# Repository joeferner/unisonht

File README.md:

# Development

## Raspberry Pi

1.  Write the latest "Raspberry Pi OS Lite" to an SD Card (enable SSH, SSH key authentication, and note the hostname)
1.  Start the Raspberry Pi, open a command prompt and `ping <hostname>.local`
1.  Open a terminal

        ssh <username>@<host>.local
        sudo apt -y install git
        # copy id_rsa from host computer
        chmod 600 ~/.ssh/id_rsa
        ssh-keygen -p -f ~/.ssh/id_rsa # remove password
        git clone git@github.com:joeferner/unisonht.git
        ./unisonht/scripts/raspberry-pi-setup.sh

1.  Install "Remote Development" extension pack for VSCode.
1.  Connect VSCode via ssh (Ctrl+Shift+P -> Remote-SSH: Connect to Host...) `<username>@<host>.local`

# Development

```
./scripts/start-dev.sh
```

# IR Remote Control

```
ir-keytable # find gpio_ir_recv and note the rcX and use it in the next command
ir-keytable -s rc1 -t -c -p all
```

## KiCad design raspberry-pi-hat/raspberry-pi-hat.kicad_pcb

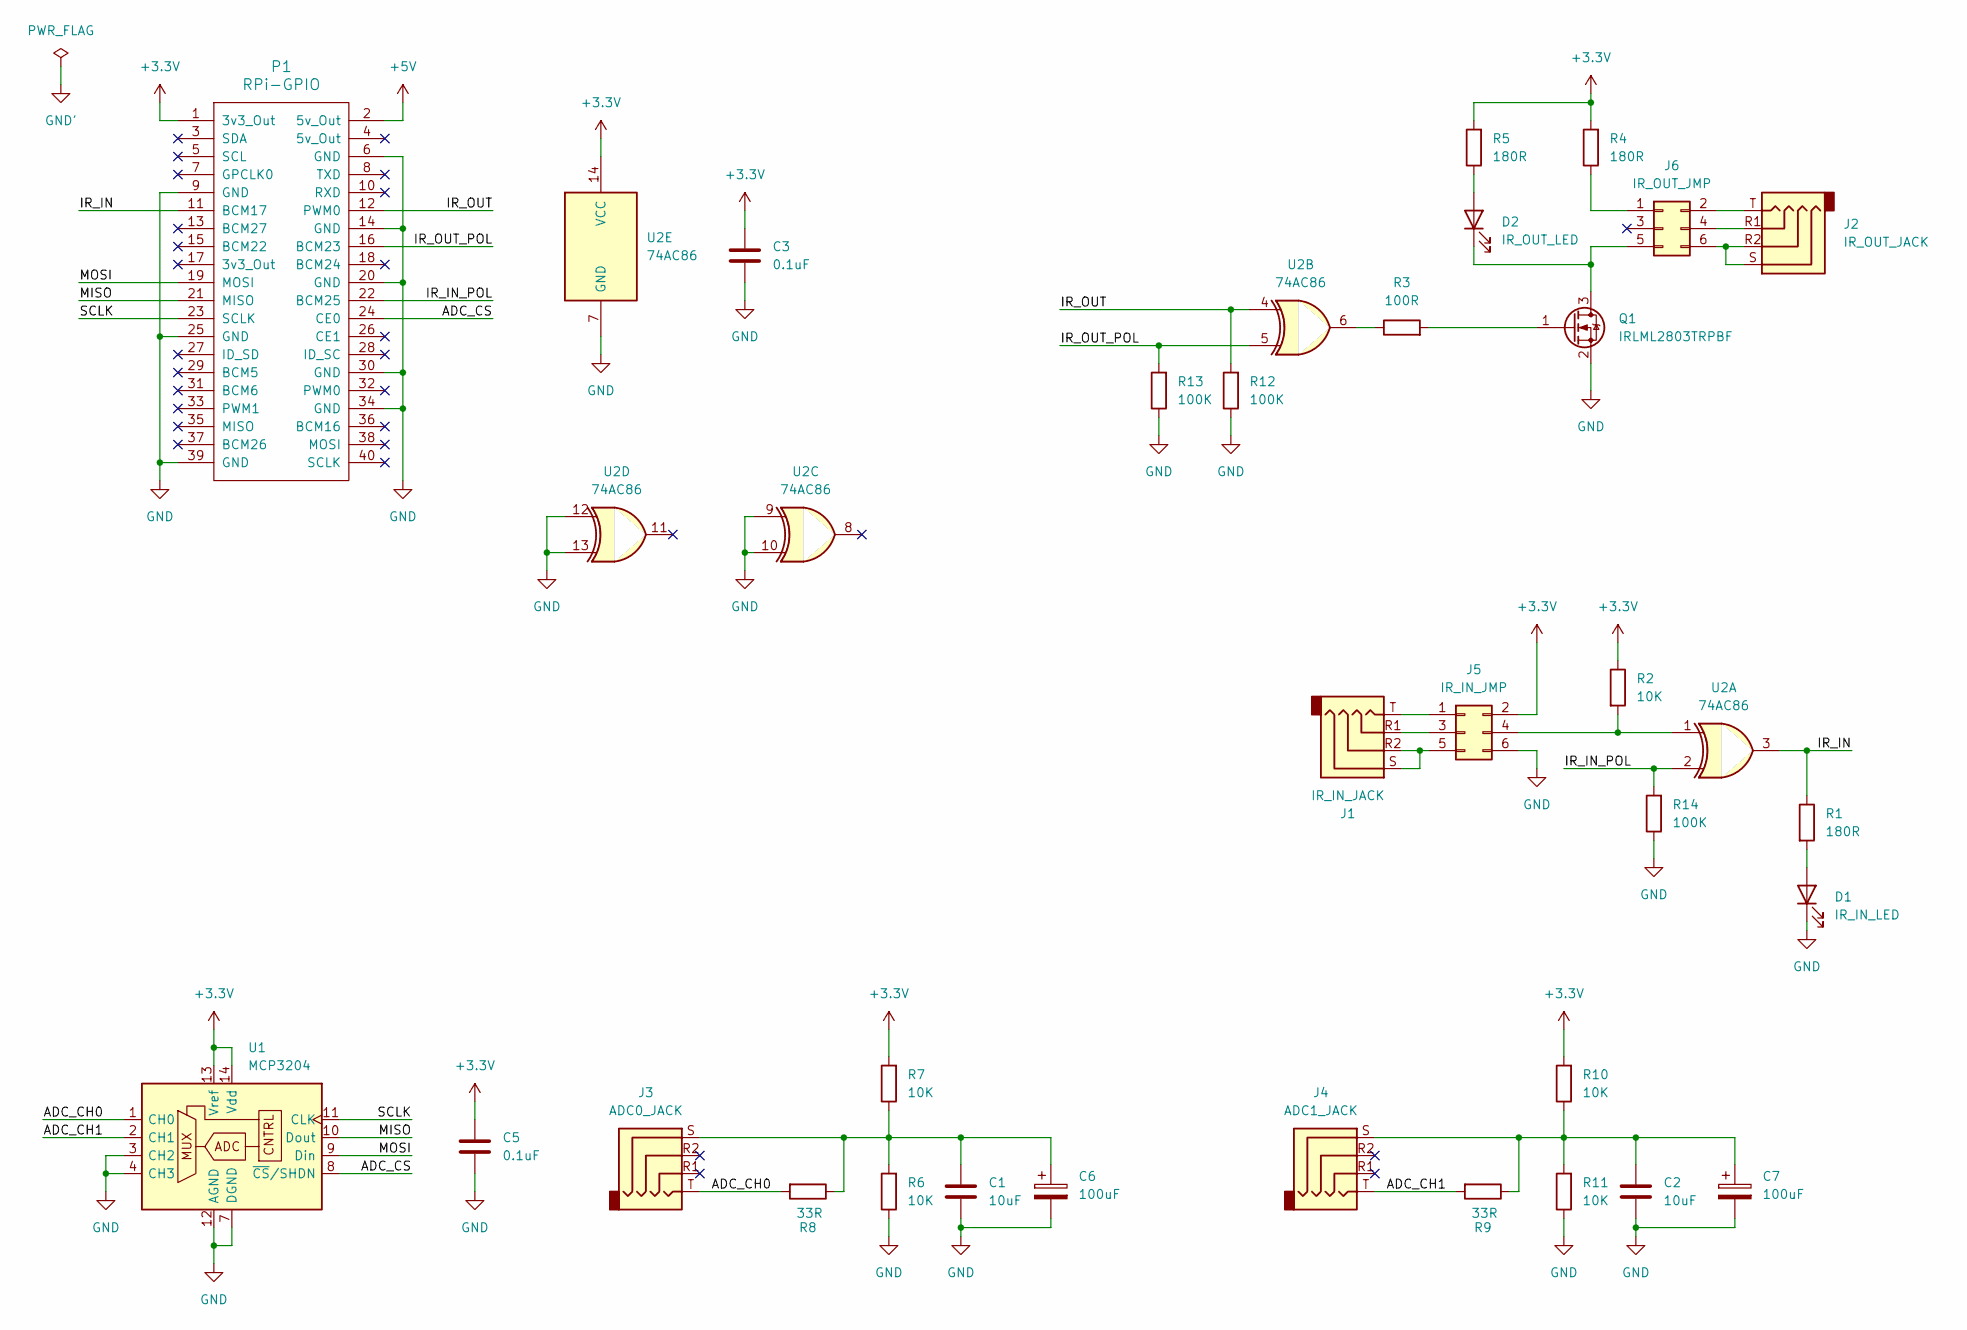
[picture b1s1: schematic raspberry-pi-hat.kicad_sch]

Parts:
C1, C2: 10uF; C_0805_2012Metric_Pad1.18x1.45mm_HandSolder
C3, C5: 0.1uF; C_0805_2012Metric_Pad1.18x1.45mm_HandSolder
C6, C7: 100uF; CP_Elec_5x5.3
D1: IR_IN_LED; LED_0805_2012Metric_Pad1.15x1.40mm_HandSolder
D2: IR_OUT_LED; LED_0805_2012Metric_Pad1.15x1.40mm_HandSolder
J1: IR_IN_JACK; 54-00174_TEN
J2: IR_OUT_JACK; 54-00174_TEN
J3: ADC0_JACK; 54-00174_TEN
J4: ADC1_JACK; 54-00174_TEN
J5: IR_IN_JMP; PinHeader_2x03_P2.54mm_Vertical
J6: IR_OUT_JMP; PinHeader_2x03_P2.54mm_Vertical
P1: RPi-GPIO; PinHeader_2x20_P2.54mm_Vertical
Q1: IRLML2803TRPBF; SOT-23
R1, R4, R5: 180R; R_0805_2012Metric_Pad1.20x1.40mm_HandSolder
R2, R6, R7, R10, R11: 10K; R_0805_2012Metric_Pad1.20x1.40mm_HandSolder
R3: 100R; R_0805_2012Metric_Pad1.20x1.40mm_HandSolder
R8, R9: 33R; R_0805_2012Metric_Pad1.20x1.40mm_HandSolder
R12, R13, R14: 100K; R_0805_2012Metric_Pad1.20x1.40mm_HandSolder
U1: MCP3204; SOIC-14_3.9x8.7mm_P1.27mm
U2: 74AC86; SOIC-14_3.9x8.7mm_P1.27mm

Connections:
+3.3V: C3.1, C5.1, J5.2, P1.1 (3v3_Out), R2.1, R4.2, R5.2, R7.2, R10.2, U1.13 (Vref), U1.14 (Vdd), U2.14 (VCC)
+5V: P1.2 (5v_Out)
/ADC_CH0: J3.T, R8.2, U1.1 (CH0)
/ADC_CH1: J4.T, R9.2, U1.2 (CH1)
/ADC_CS: P1.24 (CE0), U1.8 (~CS/SHDN)
/IR_IN: P1.11 (BCM17), R1.1, U2.3
/IR_IN_POL: P1.22 (BCM25), R14.2, U2.2
/IR_OUT: P1.12 (PWM0), R12.2, U2.4
/IR_OUT_POL: P1.16 (BCM23), R13.2, U2.5
/MISO: P1.21 (MISO), U1.10 (Dout)
/MOSI: P1.19 (MOSI), U1.9 (Din)
/SCLK: P1.23 (SCLK), U1.11 (CLK)
GND: C1.2, C2.2, C3.2, C5.2, C6.2, C7.2, D1.1 (K), J5.6, P1.6 (GND), P1.9 (GND), P1.14 (GND), P1.20 (GND), P1.25 (GND), P1.30 (GND), P1.34 (GND), P1.39 (GND), Q1.2 (S), R6.1, R11.1, R12.1, R13.1, R14.1, U1.3 (CH2), U1.4 (CH3), U1.7 (DGND), U1.12 (AGND), U2.7 (GND), U2.9, U2.10, U2.12, U2.13
unnamed: C1.1, C6.1, J3.S, R6.2, R7.1, R8.1
unnamed: C2.1, C7.1, J4.S, R9.1, R10.1, R11.2
unnamed: D1.2 (A), R1.2
unnamed: D2.2 (A), R5.1
unnamed: D2.1 (K), J6.5, Q1.3 (D)
unnamed: J1.T, J5.1
unnamed: J1.R1, J5.3
unnamed: J5.4, R2.2, U2.1
unnamed: J1.R2, J1.S, J5.5
unnamed: J6.1, R4.1
unnamed: J2.T, J6.2
unnamed: J2.R1, J6.4
unnamed: J2.R2, J2.S, J6.6
unnamed: Q1.1 (G), R3.2
unnamed: R3.1, U2.6

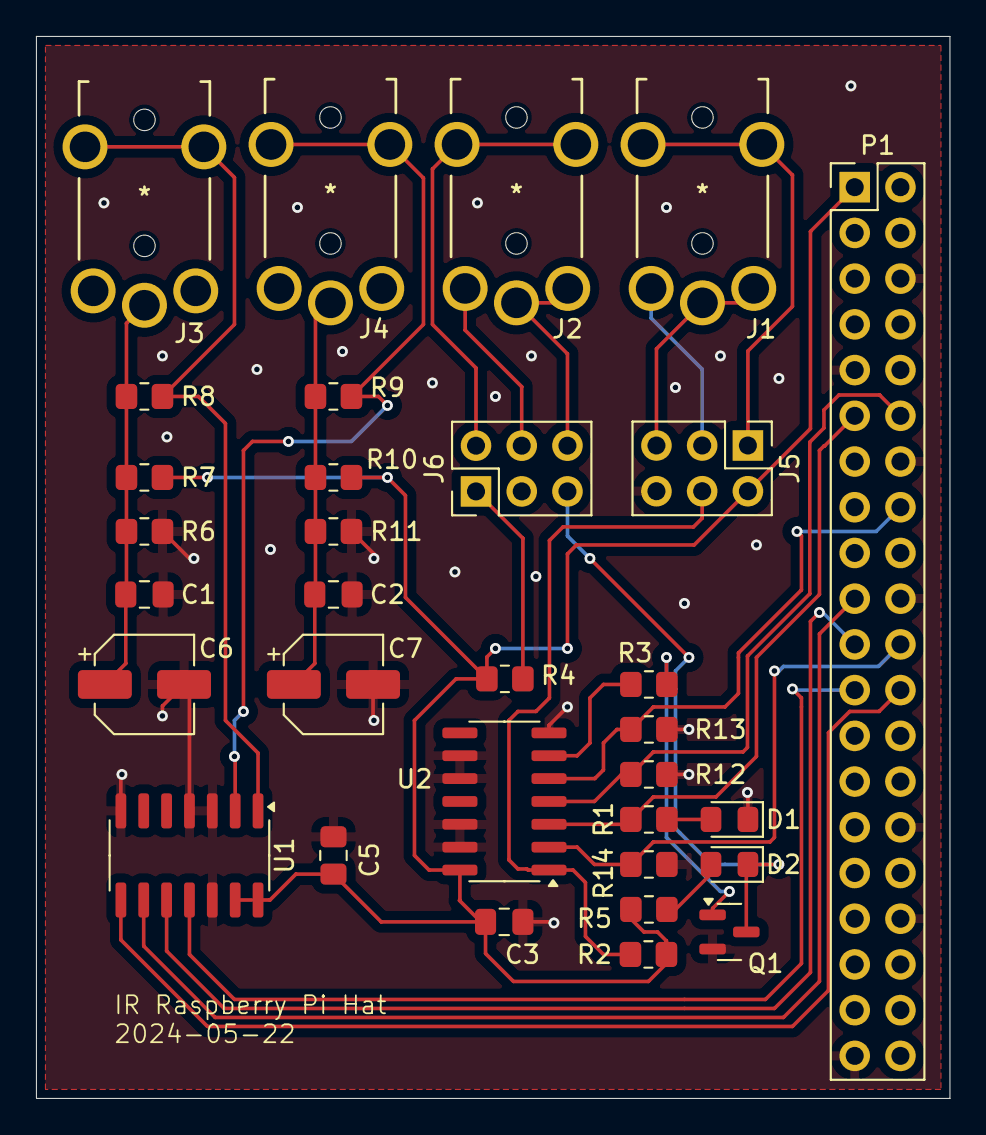
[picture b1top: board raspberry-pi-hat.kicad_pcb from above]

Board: 2 copper layers, 50.8 x 59.0 mm, 32 parts (0 on the bottom side), 27 nets.

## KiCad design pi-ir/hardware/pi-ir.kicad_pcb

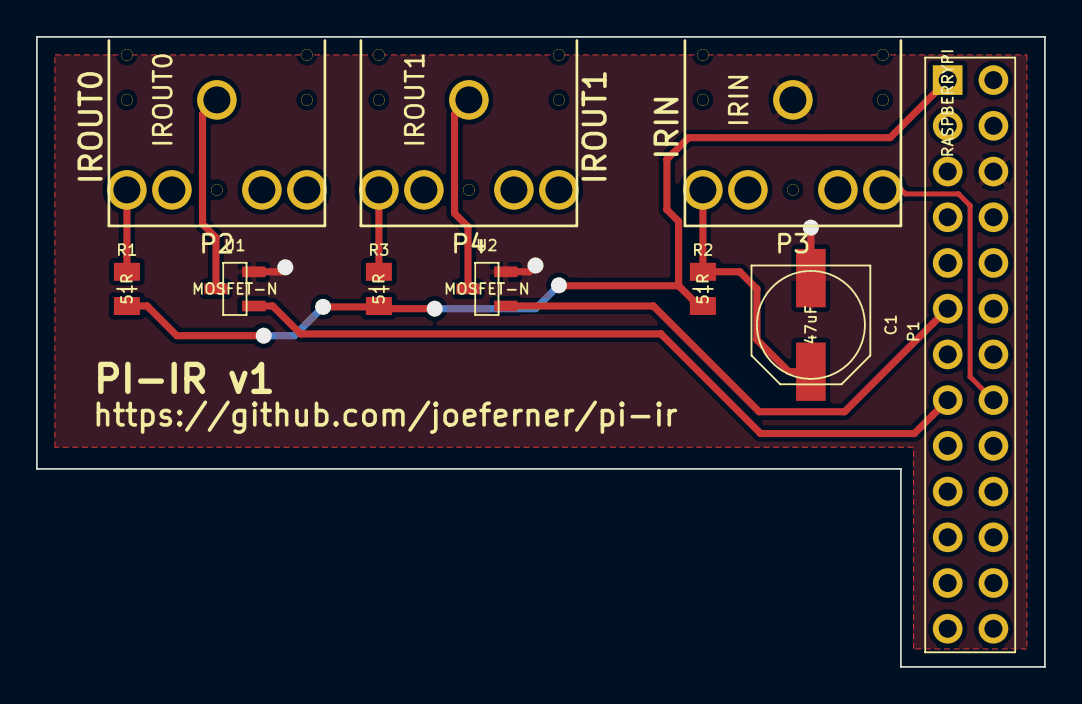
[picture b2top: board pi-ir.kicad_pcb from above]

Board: 2 copper layers, 56.0 x 35.0 mm, 10 parts (0 on the bottom side), 10 nets.

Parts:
C1: 47uF; CAPAE660X790N
P1: RASPBERRYPI; HDRV26W66P254_2X13_3297X503X838P
P2: IROUT0; SJ1-352XNG
P3: IRIN; SJ1-352XNG
P4: IROUT1; SJ1-352XNG
R1, R2, R3: 51R; RESC2012X100N
U1, U2: MOSFET-N; SOT95P237X112_123-3N

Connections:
+3.3V: P1.1, R1.1, R2.1, R3.1
/IRIN: P1.16, P3.3
/IROUT0: P1.15, U1.1
/IROUT1: P1.11, U2.1
GNDPWR: C1.2, P1.6, P3.1, U1.2, U2.2
unnamed: C1.1, P3.2, R2.2
unnamed: P2.1, U1.3
unnamed: P2.2, R1.2
unnamed: P4.1, U2.3
unnamed: P4.2, R3.2

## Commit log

2015-02-02 initial
2015-02-02 create jetty web server
2015-02-03 load config
2015-02-03 button press
2015-02-03 stub out devices
2015-02-04 working tivo
2015-02-04 kodi support working
2015-02-04 initial sony blu-ray work
2015-02-05 working lirc
2015-02-05 add try/catch for event listeners
2015-02-05 start move of web to plugin
2015-02-05 moved web into plugin
2015-02-05 add image viewer
2015-02-06 run onExit code
2015-02-07 allow args to macros
2015-02-07 help
2015-03-07 working yamaha
2015-03-08 yamaha vol up/down
2015-03-08 fix sony bluray
2015-03-27 add pi-ir
2015-03-27 switch to new kicad format
2015-03-27 update from kicad-library
2015-03-27 update hardware files
2015-03-28 readme, exception handling, config
2015-03-28 more codes
2015-03-28 fix tivo repeat
2015-03-28 fix inputs
2015-03-28 initial epson rs232
2015-03-30 update readme, fix pqiv display
2015-03-31 more screensaver instructions
2015-04-01 more tivo ir commands
2015-04-02 change to webster
2015-04-03 add ir receiver to schematic
2015-04-03 update json version
2015-04-03 fix hostname, create config dir
2015-04-03 copy all config files
2015-04-05 cleanup juds install procedures
2015-04-05 fix startup command
2015-04-05 don't copy config since the user has probably modified it anyway
2015-04-07 add logging of write command
2015-04-14 switch epson projector to http
2015-04-15 add basic status commands
2015-04-15 add xbox connection status
2015-04-15 send carrage return line feed
2015-04-15 fix projector power state
2015-04-17 more status
2015-04-17 more power status stuff
2015-04-18 fix wii
2015-04-19 parallel get status, fix xbox on detection
2015-04-19 add udp appender, add tivo error handling
2015-04-21 add to string to status
2015-04-25 main test method
2015-04-25 trying to fix epson projector
2015-04-25 refactor input to be cleaner
2015-06-10 add run and kill actions
2015-06-10 change test config
2015-06-14 switched to udp for epson
2016-11-14 increase timeout
2016-11-15 initial move to javascript
2016-11-17 working switch mode and button press
2016-11-19 updated API
2016-11-19 fix start/stop function calling
2016-11-19 prevent node shutdown
2016-11-19 remove global typescript and typings
2016-11-19 log to file
2016-11-21 fix compile, better button map
2016-11-21 log to single file
2017-01-31 add extensibility points for button presses
2017-02-02 rewrite to use Express API
2017-02-04 promise responder
2017-02-04 add test
2017-02-04 add input plugin
2017-02-04 remove pi-ir
2017-02-07 add device options
2017-02-07 add WebImageMapInput
2017-02-08 split logic into services
2017-02-10 to peer dependencies
2017-02-26 change order of powerstate so off is 0
2017-02-26 assign values to power states
2017-02-27 don't redirect to current mode if no current mode
2017-02-27 support a default mode
2017-03-22 remove outdated raspberrypi-setup.md
2017-03-25 add logstash logging
2019-08-03 inital rewrite
2019-08-09 update package lock
2019-08-09 lint
2019-08-12 settings
2019-08-13 add prompt
2019-08-13 fix web build
2019-09-15 reformat
2019-12-14 initial rewrite
2019-12-19 device url prefix
2019-12-22 denon read
2019-12-22 denon
2019-12-22 mock serialport
2020-03-15 Bump acorn from 6.2.1 to 6.4.1
    Bumps [acorn](https://github.com/acornjs/acorn) from 6.2.1 to 6.4.1.
    - [Release notes](https://github.com/acornjs/acorn/releases)
    - [Commits](https://github.com/acornjs/acorn/compare/6.2.1...6.4.1)
2020-07-17 Bump lodash from 4.17.15 to 4.17.19
    Bumps [lodash](https://github.com/lodash/lodash) from 4.17.15 to 4.17.19.
    - [Release notes](https://github.com/lodash/lodash/releases)
    - [Commits](https://github.com/lodash/lodash/compare/4.17.15...4.17.19)
2020-07-31 Bump elliptic from 6.5.0 to 6.5.3
    Bumps [elliptic](https://github.com/indutny/elliptic) from 6.5.0 to 6.5.3.
    - [Release notes](https://github.com/indutny/elliptic/releases)
    - [Commits](https://github.com/indutny/elliptic/compare/v6.5.0...v6.5.3)
2020-09-09 reformat and update versions
2020-09-09 v0.0.3
2020-09-10 raspberry-pi directions
2020-09-24 add build to pre-commit
2020-09-25 support other send types from http requests, allow switching mode
2020-09-25 get mode buttons
2020-10-09 add variants of device status to include power, volume, and input
2020-10-09 v0.0.4
2020-10-09 instructions on starting app
2021-05-10 Bump lodash from 4.17.20 to 4.17.21
    Bumps [lodash](https://github.com/lodash/lodash) from 4.17.20 to 4.17.21.
    - [Release notes](https://github.com/lodash/lodash/releases)
    - [Commits](https://github.com/lodash/lodash/compare/4.17.20...4.17.21)
2021-06-10 Bump glob-parent from 5.1.1 to 5.1.2
    Bumps [glob-parent](https://github.com/gulpjs/glob-parent) from 5.1.1 to 5.1.2.
    - [Release notes](https://github.com/gulpjs/glob-parent/releases)
    - [Changelog](https://github.com/gulpjs/glob-parent/blob/main/CHANGELOG.md)
    - [Commits](https://github.com/gulpjs/glob-parent/compare/v5.1.1...v5.1.2)
    ---
    updated-dependencies:
2021-10-22 remove javascript
2021-10-23 initial rust
2021-10-23 run actions
2021-11-11 readme
2022-03-24 Bump minimist from 1.2.5 to 1.2.6
    Bumps [minimist](https://github.com/substack/minimist) from 1.2.5 to 1.2.6.
    - [Release notes](https://github.com/substack/minimist/releases)
    - [Commits](https://github.com/substack/minimist/compare/1.2.5...1.2.6)
    ---
    updated-dependencies:
    - dependency-name: minimist
2022-04-15 add cli
2022-04-15 type check
2022-04-15 error handling
2022-04-17 graph layout
2022-04-18 select node/edge
2022-04-24 simplify
2022-04-29 roku
2022-05-01 types
2022-05-04 exports
2022-05-04 add base type
2022-05-28 openapi
2022-11-09 Bump loader-utils from 1.4.0 to 1.4.1 in /public
    Bumps [loader-utils](https://github.com/webpack/loader-utils) from 1.4.0 to 1.4.1.
    - [Release notes](https://github.com/webpack/loader-utils/releases)
    - [Changelog](https://github.com/webpack/loader-utils/blob/v1.4.1/CHANGELOG.md)
    - [Commits](https://github.com/webpack/loader-utils/compare/v1.4.0...v1.4.1)
    ---
    updated-dependencies:
2022-11-10 Bump socket.io-parser from 4.0.4 to 4.0.5 in /public
    Bumps [socket.io-parser](https://github.com/socketio/socket.io-parser) from 4.0.4 to 4.0.5.
    - [Release notes](https://github.com/socketio/socket.io-parser/releases)
    - [Changelog](https://github.com/socketio/socket.io-parser/blob/main/CHANGELOG.md)
    - [Commits](https://github.com/socketio/socket.io-parser/compare/4.0.4...4.0.5)
    ---
    updated-dependencies:
2022-11-16 Bump loader-utils from 1.4.0 to 1.4.2 in /public
    Bumps [loader-utils](https://github.com/webpack/loader-utils) from 1.4.0 to 1.4.2.
    - [Release notes](https://github.com/webpack/loader-utils/releases)
    - [Changelog](https://github.com/webpack/loader-utils/blob/v1.4.2/CHANGELOG.md)
    - [Commits](https://github.com/webpack/loader-utils/compare/v1.4.0...v1.4.2)
    ---
    updated-dependencies:
2022-11-22 Bump engine.io and socket.io in /public
    Bumps [engine.io](https://github.com/socketio/engine.io) and [socket.io](https://github.com/socketio/socket.io). These dependencies needed to be updated together.
    Updates `engine.io` from 6.1.3 to 6.2.1
    - [Release notes](https://github.com/socketio/engine.io/releases)
    - [Changelog](https://github.com/socketio/engine.io/blob/main/CHANGELOG.md)
    - [Commits](https://github.com/socketio/engine.io/compare/6.1.3...6.2.1)
    Updates `socket.io` from 4.4.1 to 4.5.3
2022-12-08 Bump decode-uri-component from 0.2.0 to 0.2.2 in /public
    Bumps [decode-uri-component](https://github.com/SamVerschueren/decode-uri-component) from 0.2.0 to 0.2.2.
    - [Release notes](https://github.com/SamVerschueren/decode-uri-component/releases)
    - [Commits](https://github.com/SamVerschueren/decode-uri-component/compare/v0.2.0...v0.2.2)
    ---
    updated-dependencies:
    - dependency-name: decode-uri-component
2023-01-02 Bump json5 from 2.2.1 to 2.2.3 in /public
    Bumps [json5](https://github.com/json5/json5) from 2.2.1 to 2.2.3.
    - [Release notes](https://github.com/json5/json5/releases)
    - [Changelog](https://github.com/json5/json5/blob/main/CHANGELOG.md)
    - [Commits](https://github.com/json5/json5/compare/v2.2.1...v2.2.3)
    ---
    updated-dependencies:
2023-01-27 Bump ua-parser-js from 0.7.31 to 0.7.33 in /public
    Bumps [ua-parser-js](https://github.com/faisalman/ua-parser-js) from 0.7.31 to 0.7.33.
    - [Release notes](https://github.com/faisalman/ua-parser-js/releases)
    - [Changelog](https://github.com/faisalman/ua-parser-js/blob/master/changelog.md)
    - [Commits](https://github.com/faisalman/ua-parser-js/compare/0.7.31...0.7.33)
    ---
    updated-dependencies:
2023-02-04 Bump http-cache-semantics from 4.1.0 to 4.1.1 in /public
    Bumps [http-cache-semantics](https://github.com/kornelski/http-cache-semantics) from 4.1.0 to 4.1.1.
    - [Release notes](https://github.com/kornelski/http-cache-semantics/releases)
    - [Commits](https://github.com/kornelski/http-cache-semantics/compare/v4.1.0...v4.1.1)
    ---
    updated-dependencies:
    - dependency-name: http-cache-semantics
2023-09-09 rewrite 2023
2023-09-11 ir recv
2023-09-11 refactor
2023-09-11 husky
2023-09-13 stage
2023-09-13 transmit
2023-09-13 transmit via rest
2023-09-13 refactor remote
2023-09-14 more denon keys
2023-09-14 openapi types
2023-09-14 udev rules
2023-09-15 remove ejs
2023-09-15 mock ir
2023-09-15 lock tx
2023-09-19 mode
2023-09-19 dark mode
2023-09-21 remove bootstrap
2023-09-21 remote tabs
2023-09-21 display name
2023-09-21 button layout
2023-09-21 order
2023-09-21 remote
2023-09-22 auto layout
2023-09-22 icons
2023-09-24 add spi support
2023-09-24 schematic
2023-09-25 fix ir gaps
2023-09-26 sharp wip
2023-09-27 sharp
2023-09-27 working denon
2023-09-30 initial schematic
2023-10-08 Bump postcss and @angular-devkit/build-angular in /public
    Bumps [postcss](https://github.com/postcss/postcss) to 8.4.31 and updates ancestor dependency [@angular-devkit/build-angular](https://github.com/angular/angular-cli). These dependencies need to be up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
    Updates `postcss` from 8.4.5 to 8.4.31
    - [Release notes](https://github.com/postcss/postcss/releases)
    - [Changelog](https://github.com/postcss/postcss/blob/main/CHANGELOG.md)
    - [Commits](https://github.com/postcss/postcss/compare/8.4.5...8.4.31)
    Updates `@angular-devkit/build-angular` from 13.3.3 to 16.2.5
2023-10-17 Bump @babel/traverse from 7.17.9 to 7.23.2 in /public
    Bumps [@babel/traverse](https://github.com/babel/babel/tree/HEAD/packages/babel-traverse) from 7.17.9 to 7.23.2.
    - [Release notes](https://github.com/babel/babel/releases)
    - [Changelog](https://github.com/babel/babel/blob/main/CHANGELOG.md)
    - [Commits](https://github.com/babel/babel/commits/v7.23.2/packages/babel-traverse)
    ---
    updated-dependencies:
2024-05-19 rewrite in rust
2024-05-19 find lirc devices
2024-05-19 read lirc
2024-05-19 decode lirc
2024-05-19 output lirc
2024-05-19 decode pioneer
2024-05-19 mode toggle
2024-05-20 mode and volume
2024-05-22 project
2024-05-22 add initial state resistors
2024-05-22 initial pcb
2024-05-23 pcb layout
2024-05-23 add gpio
2024-05-23 read power
2024-05-24 calculate on/off state
2024-05-24 print time
2024-05-24 refactor to move ir in to thread
2024-05-24 clean up power
2024-05-25 send input commands
2024-05-25 split ir writes into thread
2024-05-26 timeout ir out messages
2024-05-26 install service
2024-05-29 update instructions and setup
2024-05-29 add editor and visual to bashrc
2024-06-06 build 64
2024-06-06 add web server
2024-06-06 nvme docs
2024-06-06 slim down
2024-06-07 get state
2024-06-07 simple page
